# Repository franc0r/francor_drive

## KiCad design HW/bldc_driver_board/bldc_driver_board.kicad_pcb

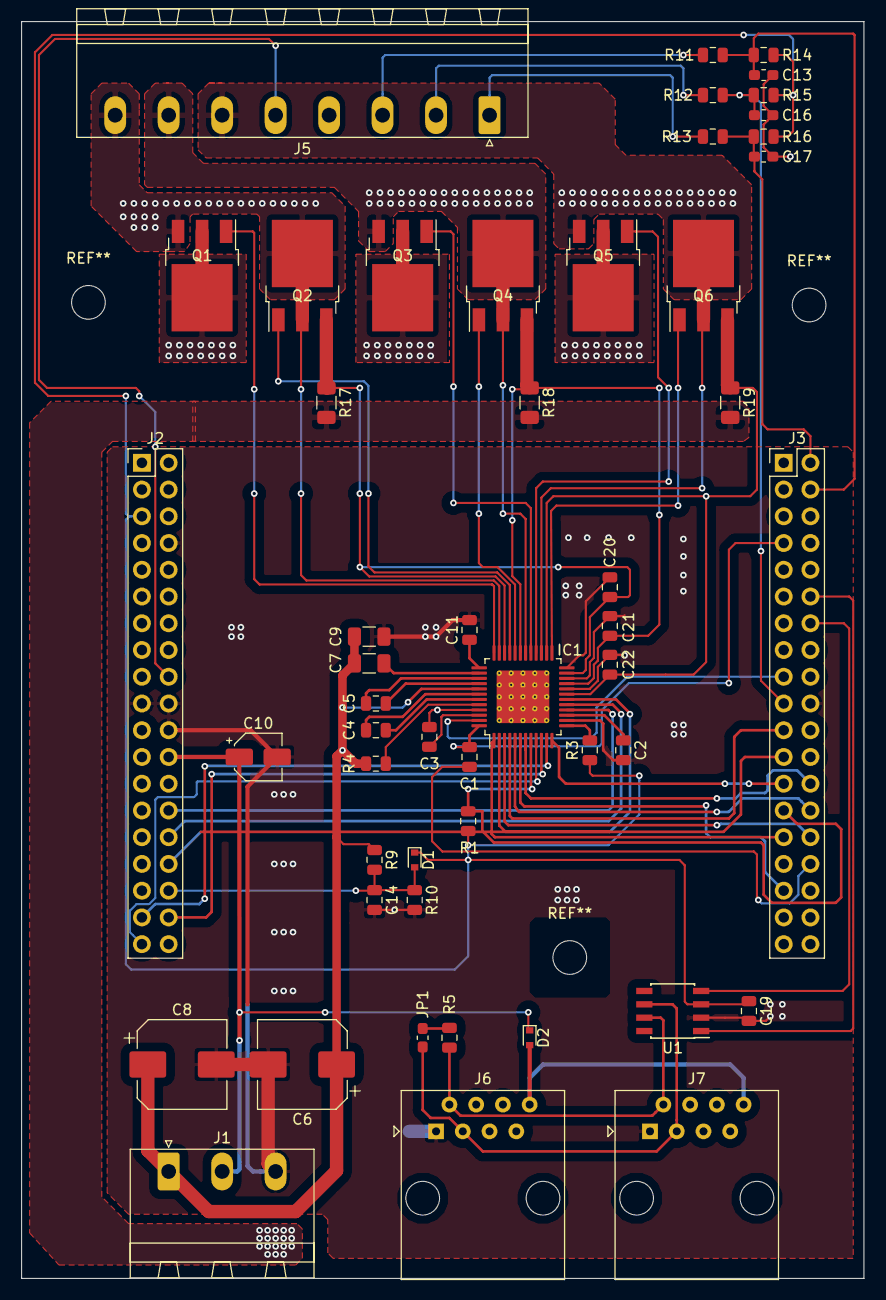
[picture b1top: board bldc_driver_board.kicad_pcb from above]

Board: 2 copper layers, 80.0 x 119.4 mm, 51 parts (0 on the bottom side), 58 nets.

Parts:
C1, C2, C3, C11, C19: 1uF; C_0805_2012Metric
C4, C5: 47nF; C_0805_2012Metric
C6, C8: 220uF; CP_Elec_8x10
C7: 2.2uF; C_1206_3216Metric
C9: 4.7uF; C_1206_3216Metric
C10: 10uF; CP_Elec_4x5.8
C13, C16, C17: 10pF; C_0603_1608Metric_Pad1.05x0.95mm_HandSolder
C14: 4.7nF; C_0805_2012Metric
C20, C21, C22: 1000pF; C_0805_2012Metric
D1, D2: BAT30KFILM; D_SOD-523
IC1: DRV8305NPHPR; TQFP-48-1EP_7x7mm_P0.5mm_EP5x5mm_ThermalVias
J1: PWR; PhoenixContact_MSTBA_2,5_3-G-5,08_1x03_P5.08mm_Horizontal
J2: N_CN7; PinHeader_2x19_P2.54mm_Vertical
J3: N_CN10; PinHeader_2x19_P2.54mm_Vertical
J5: Motor; PhoenixContact_MSTBA_2,5_8-G-5,08_1x08_P5.08mm_Horizontal
J6, J7: RJ45; RJ45_Amphenol_54602-x08_Horizontal
JP1: CAN; R_0603_1608Metric_Pad1.05x0.95mm_HandSolder
Q1, Q2, Q3, Q4, Q5, Q6: STD140N6F7; TO-252-3_TabPin2
R1, R3, R14, R15, R16: 10k; R_0805_2012Metric
R4: 100; R_0805_2012Metric
R5: 120; R_0805_2012Metric
R9: 169k; R_0805_2012Metric
R10: 9.31k; R_0805_2012Metric
R11, R12, R13: 1k; R_0805_2012Metric
R17, R18, R19: 0.002R; R_1206_3216Metric
U1: SN65HVD232; SOIC-8_3.9x4.9mm_P1.27mm

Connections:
+5V: J2.18, J5.5
+12V: C10.1, D2.1, J1.2, J2.24
+BATT: C6.1, C7.1, C8.1, C9.1, IC1.41, J1.1, Q1.2, Q3.2, Q5.2, R4.1, R9.1
/AVDD: C2.1, IC1.15
/CAN_H: J6.2, J7.2, R5.1, U1.7
/CAN_L: J6.3, J7.3, JP1.2, U1.6
/CAN_RX: J3.14, U1.4
/CAN_TX: J3.12, U1.1
/CP1H: C4.1, IC1.43
/CP1L: C4.2, IC1.42
/CP2H: C5.1, IC1.39
/CP2L: C5.2, IC1.40
/DVDD: C3.1, IC1.46
/EN_GATE: IC1.1, J3.29
/GHA: IC1.36, Q1.1
/GHB: IC1.29, Q3.1
/GHC: IC1.28, Q5.1
/GLA: IC1.33, Q2.1
/GLB: IC1.32, Q4.1
/GLC: IC1.25, Q6.1
/HALL_A: C13.1, J3.4, R11.1, R14.1
/HALL_B: C16.1, J3.19, R12.1, R15.1
/HALL_C: C17.1, J3.2, R13.1, R16.1
/HALL_IN_A: J5.3, R11.2
/HALL_IN_B: J5.2, R12.2
/HALL_IN_C: J5.1, R13.2
/INHA: IC1.2, J3.23
/INHB: IC1.4, J3.21
/INHC: IC1.6, J3.33
/INLA: IC1.3, J3.30
/INLB: IC1.5, J3.28
/INLC: IC1.7, J3.26
/PWRGD: IC1.13, R3.2
/SCLK: IC1.12, J3.25
/SDI: IC1.10, J2.36
/SDO: IC1.11, J2.35
/SHA: IC1.35, J5.8, Q1.3, Q2.2
/SHB: IC1.30, J5.7, Q3.3, Q4.2
/SHC: IC1.27, J5.6, Q5.3, Q6.2
/SLA: C20.1, IC1.23, IC1.34, Q2.3, R17.1
/SLB: C21.1, IC1.21, IC1.31, Q4.3, R18.1
/SLC: C22.1, IC1.19, IC1.26, Q6.3, R19.1
/SO1: IC1.16, J2.28
/SO2: IC1.17, J2.30
/SO3: IC1.18, J2.32
/VBUS: C14.1, D1.2, J2.34, R9.2, R10.1
/VCPH: C7.2, IC1.38
/VCP_LSD: C11.1, IC1.37
/WAKE: IC1.47, J3.17
/~FAULT: IC1.8, J3.27, R1.2
/~SCS: IC1.9, J2.37
GND: C2.2, C3.2, C6.2, C8.2, C9.2, C10.2, C11.2, C13.2, C14.2, C16.2, C17.2, C19.2, C20.2, C21.2, C22.2, IC1.14, IC1.20, IC1.22, IC1.24, IC1.45, J1.3, J2.8, J2.19, J2.20, J2.22, J3.20, J5.4, J6.1, J7.1, R10.2, R17.2, R18.2, R19.2, U1.2
GNDA: C1.2, J3.32
unnamed: D2.2, J6.8, J7.8
unnamed: IC1.44, R4.2
unnamed: JP1.1, R5.2
VDD: C19.1, D1.1, J2.5, R1.1, R3.1, R14.2, R15.2, R16.2, U1.3
VDDA: C1.1, IC1.48, J3.7

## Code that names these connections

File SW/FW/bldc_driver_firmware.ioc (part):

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Mcu.Name=STM32F446R(C-E)Tx
Mcu.Package=LQFP64
Mcu.UserName=STM32F446RETx
PA0-WKUP.GPIOParameters=GPIO_Label
PA0-WKUP.GPIO_Label=SO1
PA0-WKUP.Signal=ADCx_IN0
PA1.GPIOParameters=GPIO_Label
PA1.GPIO_Label=SO2
PA1.Signal=ADCx_IN1
PA10.GPIOParameters=GPIO_Label
PA10.GPIO_Label=INHC
PA10.Signal=S_TIM1_CH3
PA11.GPIOParameters=GPIO_Label
PA11.GPIO_Label=CAN_RX
PA11.Mode=Master
PA11.Signal=CAN1_RX
PA12.GPIOParameters=GPIO_Label
PA12.GPIO_Label=CAN_TX
PA12.Mode=Master
PA12.Signal=CAN1_TX
PA13.GPIOParameters=GPIO_Label
PA13.GPIO_Label=TMS
PA13.Mode=Serial_Wire
PA13.Signal=SYS_JTMS-SWDIO
PA14.GPIOParameters=GPIO_Label
PA14.GPIO_Label=TCK
PA14.Mode=Serial_Wire
PA14.Signal=SYS_JTCK-SWCLK
PA2.GPIOParameters=GPIO_Label
PA2.GPIO_Label=USART_TX
PA2.Mode=Asynchronous
PA2.Signal=USART2_TX
PA3.GPIOParameters=GPIO_Label
PA3.GPIO_Label=USART_RX
PA3.Mode=Asynchronous
PA3.Signal=USART2_RX
PA4.GPIOParameters=GPIO_Label
PA4.GPIO_Label=SO3
PA4.Signal=ADCx_IN4
PA5.GPIOParameters=GPIO_Label
PA5.GPIO_Label=LD2 [Green Led]
PA5.Signal=GPIO_Output
PA8.GPIOParameters=GPIO_Label
PA8.GPIO_Label=INHA
PA8.Signal=S_TIM1_CH1
PA9.GPIOParameters=GPIO_Label
PA9.GPIO_Label=INHB
PA9.Signal=S_TIM1_CH2
PB0.GPIOParameters=GPIO_Label
PB0.GPIO_Label=VBUS
PB0.Signal=ADCx_IN8
PB10.GPIOParameters=GPIO_Label
PB10.GPIO_Label=SPI_SCK
PB10.Mode=Full_Duplex_Master
PB10.Signal=SPI2_SCK
PB13.GPIOParameters=GPIO_Label
PB13.GPIO_Label=INLA
PB13.Mode=Output Compare1 CH1 CH1N
PB13.Signal=TIM1_CH1N
PB14.GPIOParameters=GPIO_Label
PB14.GPIO_Label=INLB
PB14.Mode=Output Compare2 CH2 CH2N
PB14.Signal=TIM1_CH2N
PB15.GPIOParameters=GPIO_Label
PB15.GPIO_Label=INLC
PB15.Mode=Output Compare3 CH3 CH3N
PB15.Signal=TIM1_CH3N
PB3.GPIOParameters=GPIO_Label
PB3.GPIO_Label=SWO
PB3.Signal=SYS_JTDO-SWO
PB4.GPIOParameters=GPIO_Label
PB4.GPIO_Label=nFAULT
PB4.Signal=GPIO_Input
PB5.GPIOParameters=GPIO_Label
PB5.GPIO_Label=EN_GATE
PB5.Signal=GPIO_Output
PB6.GPIOParameters=GPIO_Label
PB6.GPIO_Label=WAKE
PB6.Signal=GPIO_Output
PC1.GPIOParameters=GPIO_Label
PC1.GPIO_Label=SPI_MO
PC1.Mode=Full_Duplex_Master
PC1.Signal=SPI2_MOSI
PC13.GPIOParameters=GPIO_Label,GPIO_ModeDefaultEXTI
PC13.GPIO_Label=B1 [Blue PushButton]
PC13.GPIO_ModeDefaultEXTI=GPIO_MODE_IT_FALLING
PC13.Signal=GPXTI13
PC14-OSC32_IN.Mode=LSE-External-Oscillator
PC14-OSC32_IN.Signal=RCC_OSC32_IN
PC15-OSC32_OUT.Mode=LSE-External-Oscillator
PC15-OSC32_OUT.Signal=RCC_OSC32_OUT
PC2.GPIOParameters=GPIO_Label
PC2.GPIO_Label=SPI_MI
PC2.Mode=Full_Duplex_Master
PC2.Signal=SPI2_MISO
PC6.GPIOParameters=GPIO_Label
PC6.GPIO_Label=HALL_A
PC6.Signal=S_TIM3_CH1
PC7.GPIOParameters=GPIO_Label
PC7.GPIO_Label=HALL_B
PC7.Signal=S_TIM3_CH2
PC8.GPIOParameters=GPIO_Label
PC8.GPIO_Label=HALL_C
PC8.Signal=S_TIM3_CH3
PH0-OSC_IN.Mode=HSE-External-Oscillator
PH0-OSC_IN.Signal=RCC_OSC_IN
PH1-OSC_OUT.Mode=HSE-External-Oscillator
PH1-OSC_OUT.Signal=RCC_OSC_OUT
RCC.HSE_VALUE=8000000
RCC.SYSCLKFreq_VALUE=84000000
RCC.SYSCLKSource=RCC_SYSCLKSOURCE_PLLCLK
board=NUCLEO-F446RE
boardIOC=true

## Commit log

2019-02-16 -- Added datasheets
2019-02-16 -- Added BOM for bldc driver board
2019-02-16 -- Added example schematic
2019-02-16 -- Added schematic for BLDC driver board
2019-02-16 -- Added CubeMX project for firmware
2019-02-17 -- Continued adding BOM parts -- Removed Current Sense filtering
2019-02-17 -- Added footprings
2019-02-17 -- Fixed wrong footpring of CP
2019-02-20 -- Started PCB design -> Placed parts
2019-02-20 -- Added elecrow design rules
2019-02-20 -- Continued pcb layout
2019-02-21 -- Continued PCB design
2019-02-26 -- Continued routing and removed MOSFET Capacitors
2019-02-26 -- Added borders
2019-02-26 -- Fixed loose wire
2019-02-26 -- Fixed ground connection
2019-02-26 -- Added fields for BLDC output
2019-02-27 -- Added surfaces
2019-02-27 -- Added lines to encoder connector
2019-02-27 -- Replaced motorconnector and added drill holes
2019-02-27 -- Added thermal pads and connections to UVW
2019-02-27 -- Small fixes of planes
2019-02-27 -- Added GND Planes
2019-02-27 -- Smal changes
2019-02-28 -- Added panels for drill holes
2019-02-28 -- Fixed unwired CAN chip
2019-02-28 -- Added Gerber Files for JBLPCB Production
2019-03-04 -- Modified part list
2019-03-04 -- Added connectors to partlist
2019-03-09 -- Added comment due to forgotton resistory
2019-03-09 -- Fixed missing nSCS pin error
